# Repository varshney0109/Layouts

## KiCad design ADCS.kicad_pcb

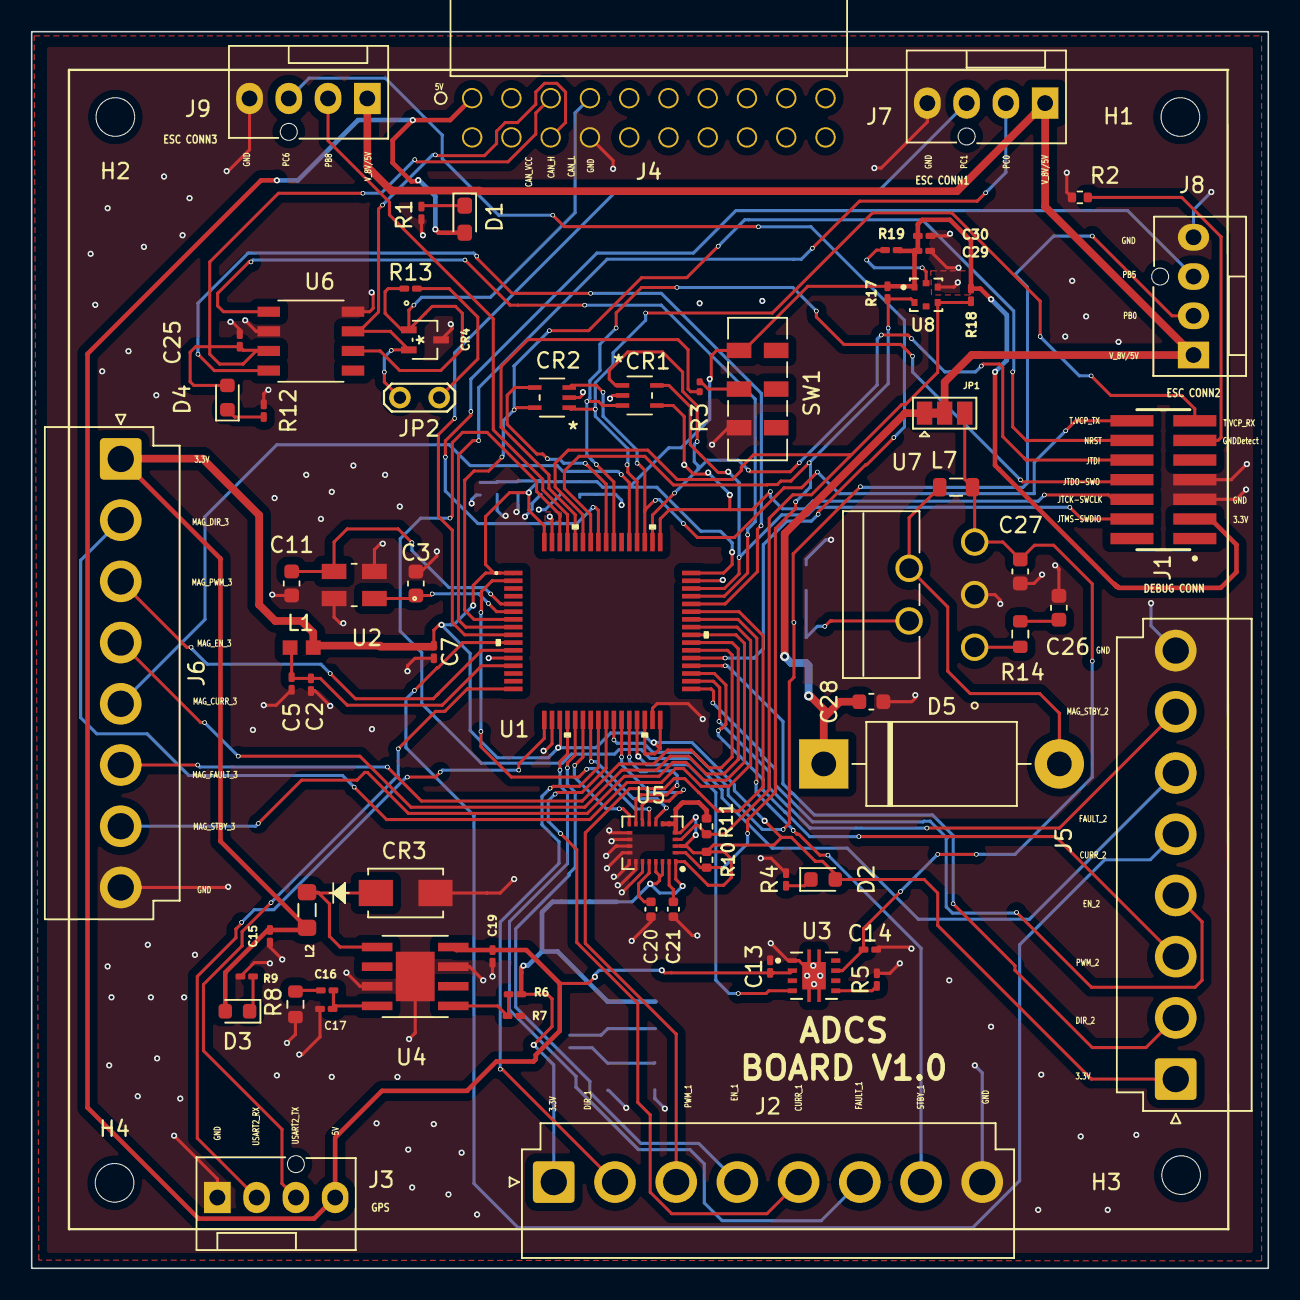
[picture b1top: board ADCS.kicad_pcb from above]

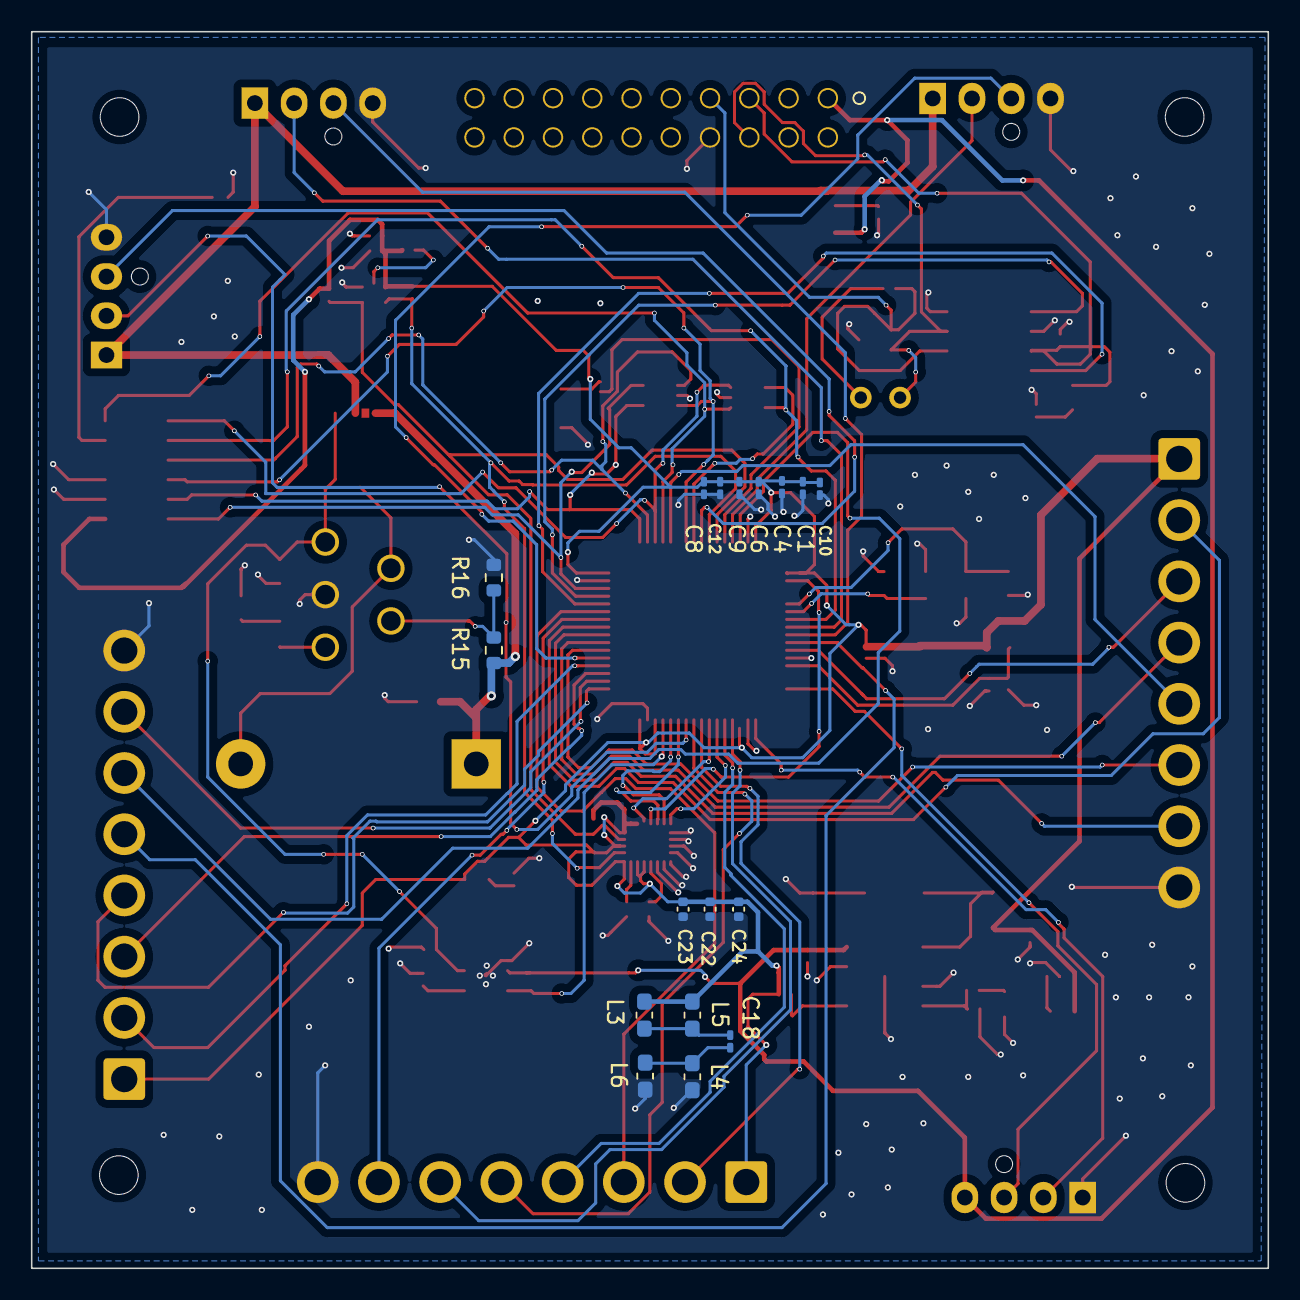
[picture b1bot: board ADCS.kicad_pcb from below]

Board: 2 copper layers, 80.0 x 80.0 mm, 89 parts (17 on the bottom side), 78 nets.

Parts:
C1, C19: 10uF; C_0201_0603Metric_Pad0.64x0.40mm_HandSolder
C2: 10nF; C_0201_0603Metric_Pad0.64x0.40mm_HandSolder
C3, C11: 0.5pF; C_0603_1608Metric
C4, C6, C7, C9, C10, C12, C18, C25, C29: 100nF; C_0201_0603Metric_Pad0.64x0.40mm_HandSolder
C5, C8: 1uF; C_0201_0603Metric_Pad0.64x0.40mm_HandSolder
C13: 0.1uF; C_0201_0603Metric_Pad0.64x0.40mm_HandSolder
C14: 68uF; C_0201_0603Metric_Pad0.64x0.40mm_HandSolder
C15: 22uF; C_0201_0603Metric_Pad0.64x0.40mm_HandSolder
C16: 68nF; C_0201_0603Metric_Pad0.64x0.40mm_HandSolder
C17: 180pF; C_0201_0603Metric_Pad0.64x0.40mm_HandSolder
C20: 10nF; C_0402_1005Metric
C21, C22: 0.1uF; C_0402_1005Metric
C23, C24: 10uF; C_0402_1005Metric
C26: 0.33uF; C_0603_1608Metric
C27: 0.1uF; C_0603_1608Metric
C28: 680uF; C_0603_1608Metric
C30: 2.2uF; C_0201_0603Metric_Pad0.64x0.40mm_HandSolder
CR1, CR2: ESDALC6V1W5
CR3: STPS1150A
CR4: ESDCAN02-2BWY
D1: LED; LED_0603_1608Metric_Pad1.05x0.95mm_HandSolder
D2, D3, D4: LED; LED_0603_1608Metric
D5: 1N5821; D_DO-201AD_P15.24mm_Horizontal
H1, H2, H3, H4: MountingHole; MountingHole_2.5mm
J1: FTSH-107-01-F-DV-K-P-TR; SAMTEC_FTSH-107-01-F-DV-K-P-TR
J2, J5, J6: Conn_01x08_Female; JST_VH_B8P-VH-B_1x08_P3.96mm_Vertical
J3, J7, J8, J9: Conn_01x04_Female; FanPinHeader_1x04_P2.54mm_Vertical
J4: Conn_02x10_Counter_Clockwise; 613020243121
JP1: Jumper_3_Bridged12; SolderJumper-3_P1.3mm_Bridged12_Pad1.0x1.5mm
JP2: Jumper_2_Bridged; TestPoint_2Pads_Pitch2.54mm_Drill0.8mm
L1: Ferrite Bead; BLM18BB121SN1D
L2: 18uH; L_0805_2012Metric_Pad1.05x1.20mm_HandSolder
L3, L4, L5, L6: 1uH; L_0603_1608Metric_Pad1.05x0.95mm_HandSolder
L7: 100uH; L_0805_2012Metric
R1, R9, R12: 1kohm; R_0201_0603Metric_Pad0.64x0.40mm_HandSolder
R2: 100ohm; R_0402_1005Metric
R3: 10kohm; R_0201_0603Metric
R4: R; R_0201_0603Metric_Pad0.64x0.40mm_HandSolder
R5: 33.3kohm; R_0201_0603Metric_Pad0.64x0.40mm_HandSolder
R6: 7.15kohm; R_0201_0603Metric_Pad0.64x0.40mm_HandSolder
R7: 4.3kohm; R_0201_0603Metric_Pad0.64x0.40mm_HandSolder
R8: 1.3kohm; R_0603_1608Metric
R10, R11: 4.7kohm; R_0402_1005Metric
R13: 120 ohm; R_0201_0603Metric_Pad0.64x0.40mm_HandSolder
R14, R16: 2.2kohm; R_0603_1608Metric
R15: 11kohm; R_0603_1608Metric
R17, R18: 4.7kohm; R_0201_0603Metric_Pad0.64x0.40mm_HandSolder
R19: 100ohm; R_0201_0603Metric_Pad0.64x0.40mm_HandSolder
SW1: SW_DPDT_x2; SW_DPDT_CK_JS202011JCQN
U1: STM32U585RIT6Q
U2: ABM8-25.000MHZ-D2Y-T
U3: TPS2557DRBR; IC_DRV8601DRBT
U4: A5975D
U5: LSM9DS1; LGA-24L_3x3.5mm_P0.43mm
U6: L9615D
U7: LM2577T-ADJ/LF03; LM2577T-ADJ&slash_LF03
U8: HTS221; XDCR_HTS221

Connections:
3.3V: C1.1, C4.1, C6.1, C7.1, C8.1, C9.1, C10.1, C12.1, C15.2, C22.2, C23.1, C24.1, C29.1, C30.1, D2.2 (A), D3.2 (A), J1.03, J2.1, J5.1, J6.1, L1.1, L2.1, L3.1, L5.2, R6.1, R10.2, R11.1, R17.1, R18.2, R19.2, SW1.3 (C), U1.1 (VBAT), U1.19 (VDD_2), U1.30 (VCAP), U1.32 (VDD_1), U1.48 (VDDUSB), U1.64 (VDD_3), U5.1 (VDDIO), U5.3 (VDDIO), U5.5 (SDO_A/G), U5.6 (SDO_M), U5.7 (CS_A/G), U5.8 (CS_M), U5.22 (VDD), U5.23 (VDD), U8.1 (VDD)
5V: C13.1, C19.2, D1.2 (A), J3.4, J4.1, U3.2 (IN), U4.8 (VCC)
/BOOST Converter/Output_8V: C28.1, D5.1 (K), JP1.1 (A), R15.1
/BOOST Converter/Vout_switch: C14.1, C27.1, JP1.3 (B), L7.1, U3.7 (OUT), U7.5 (VIN)
/CAN Transciever/CAN H: CR4.2, J4.6, JP2.2 (B), U6.7 (C_H)
/CAN Transciever/CAN L: CR4.1, J4.7, R13.1, U6.6 (C_L)
/CAN Transciever/CAN_Vcc: C25.1, D4.2 (A), J4.5, U6.3 (VS)
/CAN Transciever/FDCAN1_RX: U1.44 (PA11), U6.4 (RX0)
/CAN Transciever/FDCAN1_TX: U1.45 (PA12), U6.1 (TX0)
/ESC Connector/PB0: J8.2, U1.26 (PB0)
/ESC Connector/PB5: J8.3, U1.57 (PB5)
/ESC Connector/PB8: J9.2, U1.61 (PB8)
/ESC Connector/PC0: J7.2, U1.8 (PC0)
/ESC Connector/PC1: J7.3, U1.9 (PC1)
/ESC Connector/PC6: J9.3, U1.37 (PC6)
/ESC Connector/V_8V/5V: J7.1, J8.1, J9.1, JP1.2 (C)
/GPS Connector/USART2_RX: J3.2, U1.17 (PA3)
/GPS Connector/USART2_TX: J3.3, U1.16 (PA2)
/IMU Sensor/DEN_A/G: U1.22 (PA6), U5.13 (DEN_A/G)
/IMU Sensor/DRDY_M: U1.23 (PA7), U5.9 (DRDY_M)
/IMU Sensor/INT1_A/G: U1.27 (PB1), U5.11 (INT1_A/G)
/IMU Sensor/INT2_A/G: U1.28 (PB2), U5.12 (INT2_A/G)
/IMU Sensor/INT_M: U1.2 (PC13), U5.10 (INT_M)
/Magnetotorquer Driver1/MAG_CURR_1: J2.5, U1.25 (PC5)
/Magnetotorquer Driver1/MAG_DIR_1: J2.2, U1.24 (PC4)
/Magnetotorquer Driver1/MAG_EN_1: J2.4, U1.21 (PA5)
/Magnetotorquer Driver1/MAG_FAULT_1: J2.6, U1.20 (PA4)
/Magnetotorquer Driver1/MAG_PWM_1: J2.3, U1.43 (PA10)
/Magnetotorquer Driver1/MAG_STBY_1: J2.7, U1.42 (PA9)
/Magnetotorquer Driver2/MAG_CURR_2: J5.5, U1.10 (PC2)
/Magnetotorquer Driver2/MAG_DIR_2: J5.2, U1.36 (PB15)
/Magnetotorquer Driver2/MAG_EN_2: J5.4, U1.33 (PB12)
/Magnetotorquer Driver2/MAG_FAULT_2: J5.6, U1.62 (PB9)
/Magnetotorquer Driver2/MAG_PWM_2: J5.3, U1.35 (PB14)
/Magnetotorquer Driver2/MAG_STBY_2: J5.7, U1.34 (PB13)
/Magnetotorquer Driver3/MAG_CURR_3: J6.5, U1.53 (PC12)
/Magnetotorquer Driver3/MAG_DIR_3: J6.2, U1.41 (PA8)
/Magnetotorquer Driver3/MAG_EN_3: J6.4, U1.39 (PC8)
/Magnetotorquer Driver3/MAG_FAULT_3: J6.6, U1.38 (PC7)
/Magnetotorquer Driver3/MAG_PWM_3: J6.3, U1.11 (PC3)
/Magnetotorquer Driver3/MAG_STBY_3: J6.7, U1.40 (PC9)
/Main_Microcontroller/DEBUG_JTCK-SWCLK: CR1.4 (I/O3), J1.06, U1.49 (PA14)
/Main_Microcontroller/DEBUG_JTDI: CR1.1 (I/O1), J1.10, U1.50 (PA15)
/Main_Microcontroller/DEBUG_JTDO-SWO: CR1.3 (I/O2), J1.08, U1.55 (PB3)
/Main_Microcontroller/DEBUG_JTMS-SWDIO: CR1.5 (I/O4), J1.04, U1.46 (PA13)
/Main_Microcontroller/DEBUG_JTRST: CR2.4 (I/O3), U1.56 (PB4)
/Main_Microcontroller/ENABLE: U1.29 (PB10), U3.4 (EN)
/Main_Microcontroller/GNDDetect: J1.11, R2.2
/Main_Microcontroller/NRST: CR2.5 (I/O4), J1.12, U1.7 (NRST)
/Main_Microcontroller/PH3-BOOT0: R3.1, U1.60 (PH3-BOOT0)
/Main_Microcontroller/T.VCP_RX: CR2.1 (I/O1), J1.13, U1.52 (PC11)
/Main_Microcontroller/T.VCP_TX: CR2.3 (I/O2), J1.14, U1.51 (PC10)
GND: C1.2, C2.2, C3.2, C4.2, C5.2, C6.2, C7.2, C8.2, C9.2, C10.2, C11.1, C12.2, C13.2, C14.2, C15.1, C17.1, C19.1, C20.2, C21.2, C22.1, C23.2, C24.2, C25.2, C26.2, C27.2, C28.2, C29.2, C30.2, CR1.2 (GND), CR2.2 (GND), CR3.2, CR4.3, J1.05, J1.07, J2.8, J3.1, J4.8, J5.8, J6.8, J7.4, J8.4, J9.4, L4.1, L6.2, R1.2, R2.1, R4.2, R5.2, R7.1, R8.1, R9.1, R12.2, R16.2, SW1.1 (A), U1.12 (VSSA), U1.18 (VSS), U1.31 (VSS_1), U1.47 (VSS_2), U1.63 (VSS_3), U2.2, U2.4, U3.1 (GND), U3.9 (EPAD), U4.3 (INH), U4.7 (GND), U4.EPAD (GND), U5.14 (RES), U5.15 (RES), U5.16 (RES), U5.17 (RES), U5.18 (RES), U5.19 (GND), U5.20 (GND), U6.2 (GND), U6.8 (ASC), U7.3 (GROUND), U8.5 (GND)
I2C1_SCL: R10.1, R17.2, U1.58 (PB6), U5.2 (SCL/SPC), U8.2 (SCL/SPC)
I2C1_SDA: R11.2, R18.1, U1.59 (PB7), U5.4 (SDA/SDI/SDO), U8.4 (SDA/SDI/SDO)
unnamed: C2.1, C5.1, L1.2, U1.13 (VDDA)
unnamed: C3.1, U1.6 (PH1-OSC_OUT), U2.1
unnamed: C11.2, U1.5 (PH0-OSC_IN), U2.3
unnamed: C16.1, R8.2
unnamed: C16.2, C17.2, U4.4 (COMP)
unnamed: C18.1, L3.2, L5.1
unnamed: C18.2, L4.2, L6.1
unnamed: C20.1, U5.21 (CAP)
unnamed: C21.1, U5.24 (C1)
unnamed: C26.1, R14.2
unnamed: CR3.1, L2.2, U4.1 (OUT)
unnamed: D1.1 (K), R1.1
unnamed: D2.1 (K), R4.1
unnamed: D3.1 (K), R9.2
unnamed: D4.1 (K), R12.1
unnamed: D5.2 (A), L7.2, U7.4 (SWITCH)
unnamed: JP2.1 (A), R13.2
unnamed: R3.2, SW1.2 (B)
unnamed: R5.1, U3.5 (ILIM)
unnamed: R6.2, R7.2, U4.5 (FB)
unnamed: R14.1, U7.1 (COMP)
unnamed: R15.2, R16.1, U7.2 (FEEDBACK)
unnamed: R19.1, U8.6 (CS)

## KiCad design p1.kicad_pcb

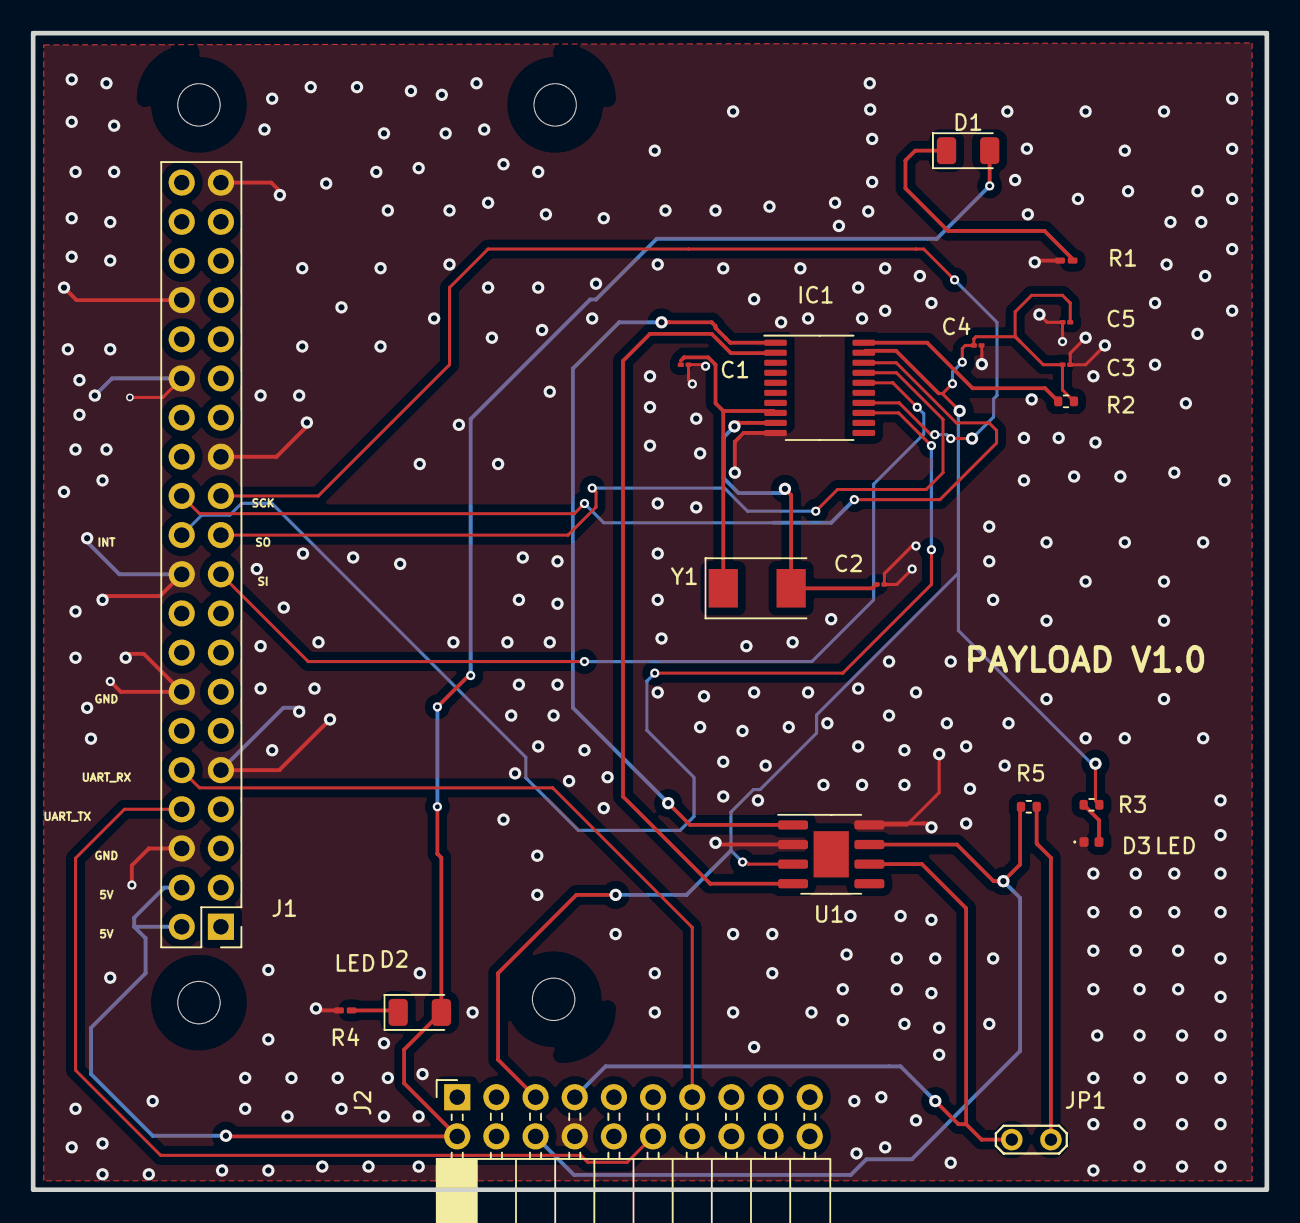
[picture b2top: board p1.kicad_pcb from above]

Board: 2 copper layers, 80.0 x 75.0 mm, 19 parts (0 on the bottom side), 21 nets.

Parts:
C1, C2: 22pF; C_01005_0402Metric
C3: 10uF/16V; C_01005_0402Metric
C4, C5: 0.1uF; C_01005_0402Metric
D1, D2: LED; LED_1206_3216Metric
D3: LED; LED_0402_1005Metric
IC1: MCP2515-xST; TSSOP-20_4.4x6.5mm_P0.65mm
J1: Connector_Generic_Conn_02x20_Odd_Even; PinHeader_2x20_P2.54mm_Vertical
J2: Conn_01x20_Male; PinSocket_2x10_P2.54mm_Horizontal
JP1: Jumper_1_Open; TestPoint_2Pads_Pitch2.54mm_Drill0.8mm
R1, R4: 1kohm; R_0201_0603Metric_Pad0.64x0.40mm_HandSolder
R2: 10K; R_0402_1005Metric
R3: 1K; R_0402_1005Metric
R5: 120; R_0402_1005Metric
U1: L9615D; SOIC-8-1EP_3.9x4.9mm_P1.27mm_EP2.29x3mm
Y1: 8MHz; Crystal_SMD_0603-2Pin_6.0x3.5mm

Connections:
5V: D1.2 (A), D2.2 (A), J1.2, J1.4, J2.2
/CS: IC1.18 (~CS), J1.24
/SCK: IC1.14 (SCK), J1.23
/SI: IC1.16 (SI), J1.19
/SO: IC1.17 (SO), J1.21
CAN_H: J2.6, R5.1, U1.7 (C_H)
CAN_L: J2.7, JP1.2 (B), U1.6 (C_L)
CAN_VCC: C3.2, C4.2, C5.2, IC1.19 (~RESET), J2.5, R2.1, R3.1, U1.3 (VS)
GND: C1.2, C2.2, C3.1, C4.1, C5.1, D3.1 (K), IC1.10 (VSS), J1.6, J1.9, J1.14, J1.20, J1.25, J1.30, J1.34, J1.39, J2.8, R1.1, R4.2, U1.2 (GND), U1.8 (ASC)
INT: IC1.13 (~INT), J1.22
unnamed: C1.1, IC1.8 (OSC2), Y1.1
unnamed: C2.1, IC1.9 (OSC1), Y1.2
unnamed: D1.1 (K), R1.2
unnamed: D2.1 (K), R4.1
unnamed: D3.2 (A), R3.2
unnamed: IC1.1 (TXCAN), U1.1 (TX0)
unnamed: IC1.2 (RXCAN), U1.4 (RX0)
unnamed: IC1.20 (VDD), R2.2
unnamed: JP1.1 (A), R5.2
UART_RX: J1.10, J2.13
UART_TX: J1.8, J2.12

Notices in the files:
parts and their libraries:
Copyright 2021 Accelerated Designs. All rights reserved.
